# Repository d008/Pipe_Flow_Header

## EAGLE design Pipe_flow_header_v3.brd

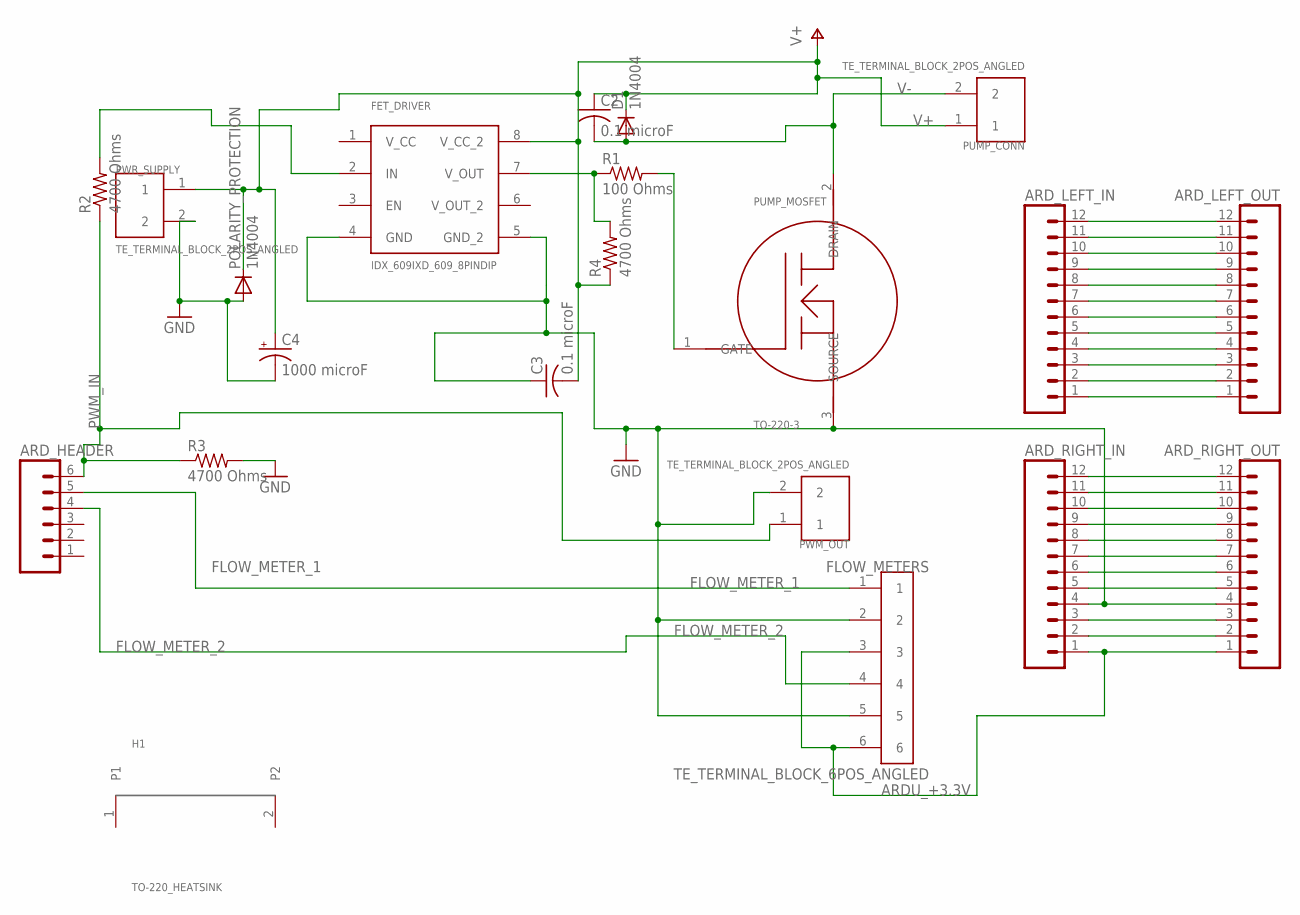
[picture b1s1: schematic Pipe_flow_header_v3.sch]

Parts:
ARD_HEADER: M06LONGPADS; 1X06_LONGPADS
ARD_LEFT_IN: M12LOCK_LONGPADS; 1X12_LOCK_LONGPADS
ARD_LEFT_OUT: M12LOCK_LONGPADS; 1X12_LOCK_LONGPADS
ARD_RIGHT_IN: M12LOCK_LONGPADS; 1X12_LOCK_LONGPADS
ARD_RIGHT_OUT: M12LOCK_LONGPADS; 1X12_LOCK_LONGPADS
C2, C3: 0.1 microF; C075-032X103
C4: 1000 microF; E7,5-16
D1: 1N4004; DO41-10
FET_DRIVER: IDX_609IXD_609_8PINDIP; IDX_609_8PINDIP
FLOW_METERS: TE_TERMINAL_BLOCK_6POS_ANGLED
H1: TO-220_HEATSINK
POLARITY_PROTECTION: 1N4004; DO41-10
PUMP_CONN: TE_TERMINAL_BLOCK_2POS_ANGLED
PUMP_MOSFET: TO-220-3
PWM_OUT: TE_TERMINAL_BLOCK_2POS_ANGLED
PWR_SUPPLY: TE_TERMINAL_BLOCK_2POS_ANGLED
R1: 100 Ohms; 0204/7
R2, R3, R4: 4700 Ohms; 0204/7

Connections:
ARDU_+3.3V: ARD_RIGHT_IN.1, ARD_RIGHT_OUT.1, FLOW_METERS.3, FLOW_METERS.6
FLOW_METER_1: ARD_HEADER.5, FLOW_METERS.1
FLOW_METER_2: ARD_HEADER.4, FLOW_METERS.4
GATE: PUMP_MOSFET.1 (GATE), R1.2
GND: ARD_RIGHT_IN.4, ARD_RIGHT_OUT.4, C3.1, C4.-, FET_DRIVER.4 (GND), FET_DRIVER.5 (GND_2), FLOW_METERS.2, FLOW_METERS.5, POLARITY_PROTECTION.A, PUMP_MOSFET.3 (SOURCE), PWM_OUT.2, PWR_SUPPLY.2, R3.2
unnamed: ARD_LEFT_IN.1, ARD_LEFT_OUT.1
unnamed: ARD_LEFT_IN.2, ARD_LEFT_OUT.2
unnamed: ARD_LEFT_IN.3, ARD_LEFT_OUT.3
unnamed: ARD_LEFT_IN.12, ARD_LEFT_OUT.12
unnamed: ARD_LEFT_IN.4, ARD_LEFT_OUT.4
unnamed: ARD_LEFT_IN.5, ARD_LEFT_OUT.5
unnamed: ARD_LEFT_IN.6, ARD_LEFT_OUT.6
unnamed: ARD_LEFT_IN.7, ARD_LEFT_OUT.7
unnamed: ARD_LEFT_IN.8, ARD_LEFT_OUT.8
unnamed: ARD_LEFT_IN.9, ARD_LEFT_OUT.9
unnamed: ARD_LEFT_IN.10, ARD_LEFT_OUT.10
unnamed: ARD_LEFT_IN.11, ARD_LEFT_OUT.11
unnamed: FET_DRIVER.7 (V_OUT), R1.1, R4.2
unnamed: FET_DRIVER.2 (IN), R2.2
unnamed: ARD_RIGHT_IN.2, ARD_RIGHT_OUT.2
unnamed: ARD_RIGHT_IN.3, ARD_RIGHT_OUT.3
unnamed: ARD_RIGHT_IN.5, ARD_RIGHT_OUT.5
unnamed: ARD_RIGHT_IN.6, ARD_RIGHT_OUT.6
unnamed: ARD_RIGHT_IN.7, ARD_RIGHT_OUT.7
unnamed: ARD_RIGHT_IN.8, ARD_RIGHT_OUT.8
unnamed: ARD_RIGHT_IN.9, ARD_RIGHT_OUT.9
unnamed: ARD_RIGHT_IN.10, ARD_RIGHT_OUT.10
unnamed: ARD_RIGHT_IN.11, ARD_RIGHT_OUT.11
unnamed: ARD_RIGHT_IN.12, ARD_RIGHT_OUT.12
PWM_IN: ARD_HEADER.6, PWM_OUT.1, R2.1, R3.1
V+: C2.1, C3.2, C4.+, D1.C, FET_DRIVER.8 (V_CC_2), POLARITY_PROTECTION.C, PUMP_CONN.1, PWR_SUPPLY.1, R4.1
V-: C2.2, D1.A, PUMP_CONN.2, PUMP_MOSFET.2 (DRAIN)

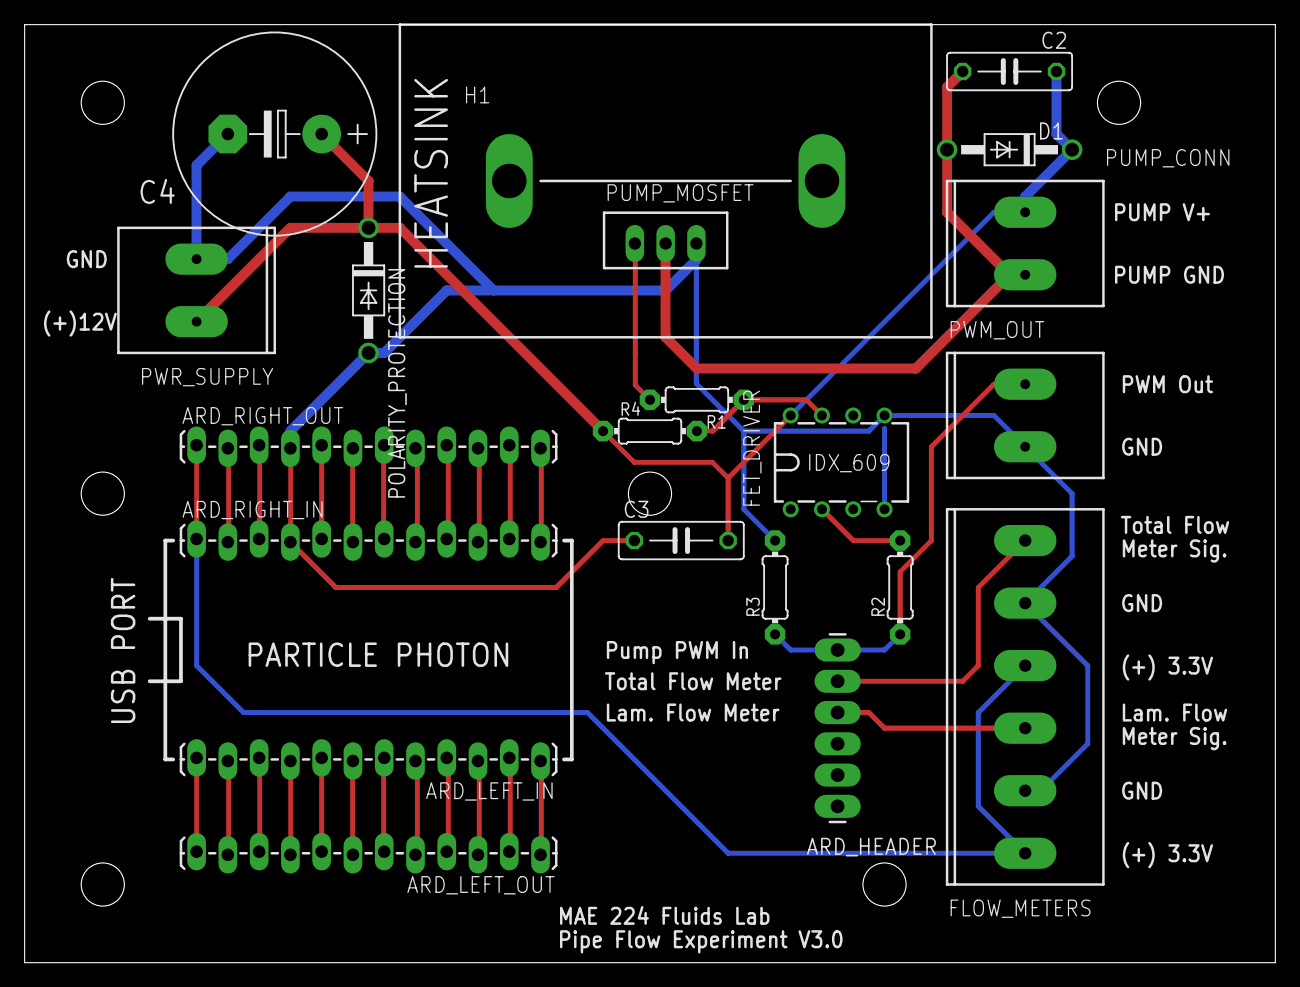
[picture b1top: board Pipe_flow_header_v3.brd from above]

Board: 2 copper layers, 101.6 x 76.2 mm, 21 parts (0 on the bottom side), 32 nets.

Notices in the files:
parts and their libraries:
SparkFun-Connectors: Licensing: Creative Commons ShareAlike 4.0 International - https://creativecommons.org/licenses/by-sa/4.0
